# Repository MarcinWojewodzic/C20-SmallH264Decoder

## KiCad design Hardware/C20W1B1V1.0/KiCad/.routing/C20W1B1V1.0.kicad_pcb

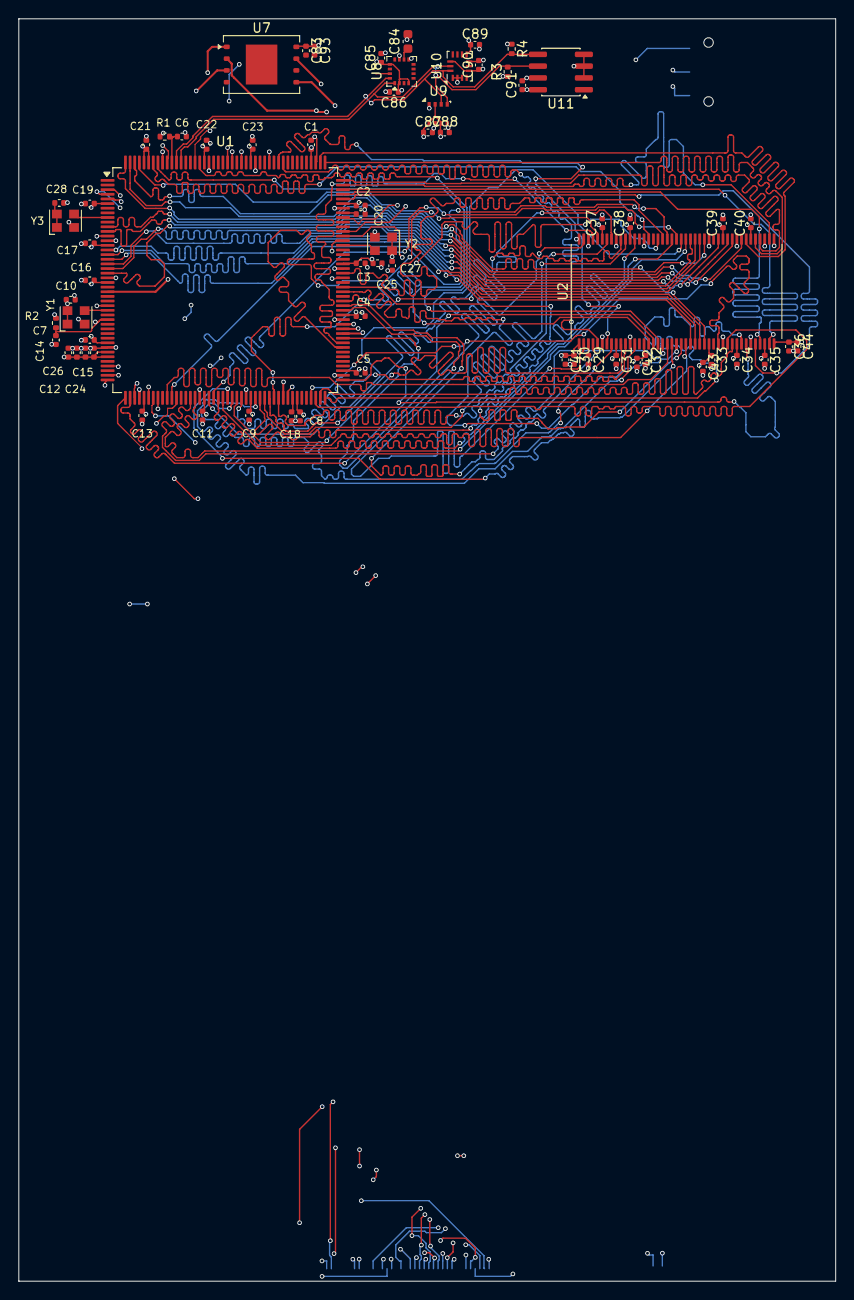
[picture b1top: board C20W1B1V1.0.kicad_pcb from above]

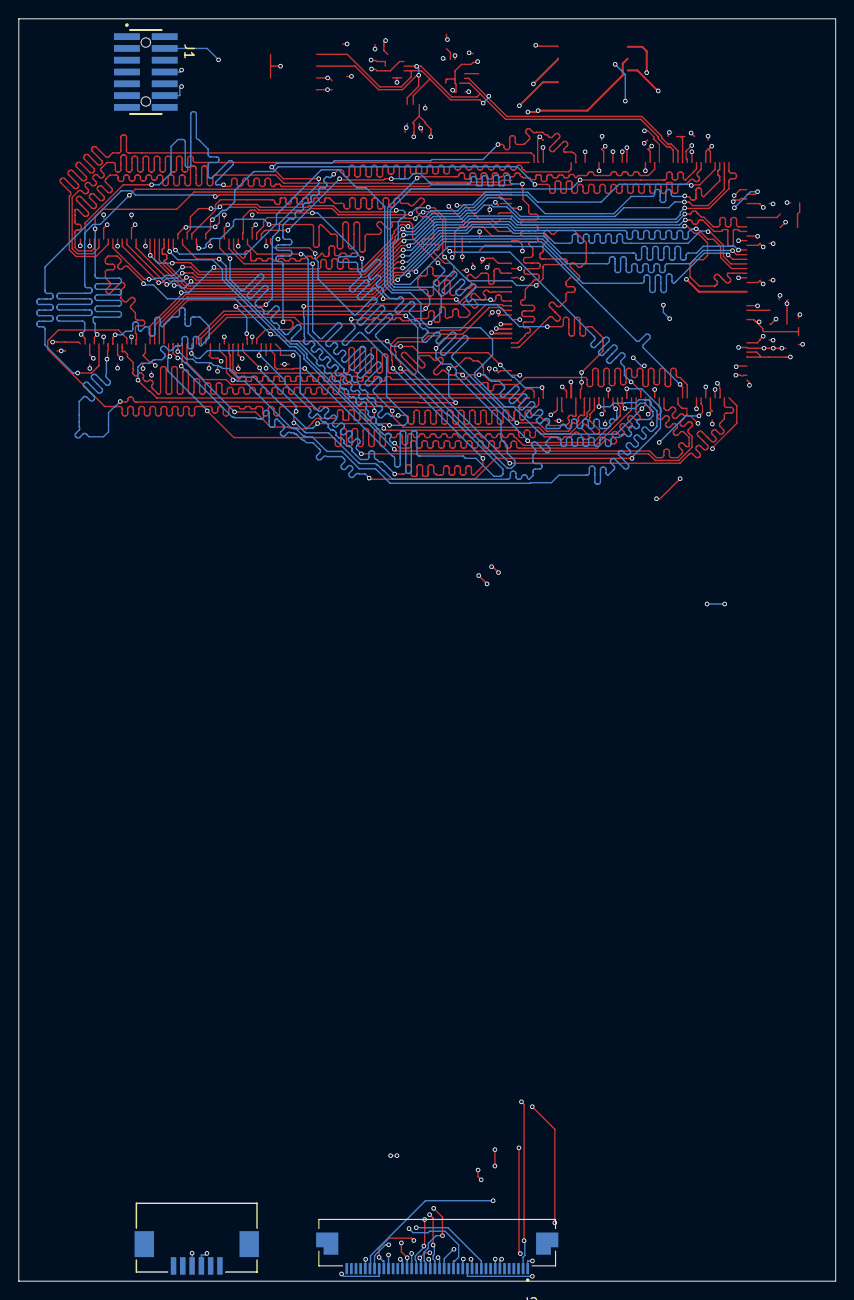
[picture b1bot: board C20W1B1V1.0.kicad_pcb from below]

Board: 6 copper layers, 88.0 x 136.0 mm, 71 parts (3 on the bottom side), 110 nets.

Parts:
C1, C2, C3, C4, C5, C6, C7, C8, C9, C10, C11, C13, C14, C15, C16, C17, C19, C21, C22, C23, C24, C27, C28, C29, C30, C31, C32, C33, C34, C35, C36, C37, C38, C39, C40, C83: 100n/50V/X5R; C_0402_1005Metric
C12, C18, C20, C25, C26, C41, C42, C43, C44, C93: 2u2/10V/X5R; C_0402_1005Metric
C84: 10u/10V/X5R; C_0603_1608Metric
C85, C86, C87, C88, C89, C90, C91: 4.7u/10V/X5R; C_0402_1005Metric
J1: FTSH-107-01-L-DV-K-A; SAMTEC_FTSH-107-01-L-DV-K-A
J2: 62684-402100ALF; AMPHENOL_62684-402100ALF
J3: 0522710679; CON_522710679_MOL
R1, R2: 10k/1%/0.063W; R_0402_1005Metric
R3, R4: 4k7/1%/0.063W; R_0402_1005Metric
U1: STM32H753IITx; LQFP-176_24x24mm_P0.5mm
U2: IS45S32400J-6TLA1-TR; TSOP-II-86_10.16x22.22mm_P0.5mm_ISSI
U7: W25R256JVEIQ; WSON-8-1EP_8x6mm_P1.27mm_EP3.4x4.3mm
U8: MMC5983MA; LGA-16_3x3mm_P0.5mm
U9: BME280; Bosch_LGA-8_2.5x2.5mm_P0.65mm_ClockwisePinNumbering
U10: LSM6DSV80XTR; Bosch_LGA-14_3x2.5mm_P0.5mm
U11: FM24CL04B-GTR; SOIC-8_3.9x4.9mm_P1.27mm
Y1: XO22C3EREHX25M000; Oscillator_SMD_Kyocera_KC2520Z-4Pin_2.5x2.0mm
Y2: KC2520Z12.2880C1KX00; Oscillator_SMD_Kyocera_KC2520Z-4Pin_2.5x2.0mm
Y3: ECS-327MVATX-2-CN-TR; Oscillator_SMD_Kyocera_KC2520Z-4Pin_2.5x2.0mm

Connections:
+3V3: C1.1, C2.1, C3.1, C4.1, C5.1, C8.1, C9.1, C10.1, C11.1, C12.1, C13.1, C14.1, C15.1, C16.1, C17.1, C19.1, C21.1, C22.1, C23.1, C24.1, C25.1, C26.1, C27.1, C28.1, C29.1, C30.1, C31.1, C32.1, C33.1, C34.1, C35.1, C36.1, C37.1, C38.1, C39.1, C40.1, C41.1, C42.1, C43.1, C44.1, C83.1, C85.1, C86.1, C87.1, C88.1, C89.1, C90.1, C91.1, C93.1, J1.3 (VCC), J2.4, J3.1, R2.1, R3.1, R4.1, U1.6 (VBAT), U1.15 (VDD), U1.23 (VDD), U1.36 (VDD), U1.38 (VREF+), U1.39 (VDDA), U1.49 (VDD), U1.62 (VDD), U1.72 (VDD), U1.82 (VDD), U1.91 (VDD), U1.103 (VDD), U1.114 (VDD33_USB), U1.127 (VDD), U1.136 (VDD), U1.149 (VDD), U1.159 (VDD), U1.171 (PDR_ON), U1.172 (VDD), U2.1 (VDD), U2.3 (VDDQ), U2.9 (VDDQ), U2.15 (VDD), U2.29 (VDD), U2.35 (VDDQ), U2.41 (VDDQ), U2.43 (VDD), U2.49 (VDDQ), U2.55 (VDDQ), U2.75 (VDDQ), U2.81 (VDDQ), U7.8 (VCC), U8.2 (VDD), U8.4 (SPI_CS), U8.13 (VDDIO), U9.2 (CSB), U9.6 (VDDIO), U9.8 (VDD), U10.5 (VDDIO), U10.8 (VDD), U10.12 (CS), U11.8 (VDD), Y1.1 (INH), Y1.4 (VCC), Y2.1 (INH), Y2.4 (VCC), Y3.1 (INH), Y3.4 (VCC)
/uC/RX: J1.14 (VCP_TX), U1.140 (PC11)
/uC/STM_NRST: C7.1, J1.12 (~RST), R2.2, U1.31 (NRST)
/uC/SWCLK: J1.6 (JCLK/SWCLK), U1.137 (PA14)
/uC/SWDIO: J1.4 (JTMS/SWDIO), U1.124 (PA13)
/uC/SWO: J1.8 (JTDO/SWO), U1.161 (PB3)
/uC/TX: J1.13 (VCP_RX), U1.139 (PC10)
FMC_A0: U1.16 (PF0), U2.25 (A0)
FMC_A1: U1.17 (PF1), U2.26 (A1)
FMC_A2: U1.18 (PF2), U2.27 (A2)
FMC_A3: U1.19 (PF3), U2.60 (A3)
FMC_A4: U1.20 (PF4), U2.61 (A4)
FMC_A5: U1.21 (PF5), U2.62 (A5)
FMC_A6: U1.60 (PF12), U2.63 (A6)
FMC_A7: U1.63 (PF13), U2.64 (A7)
FMC_A8: U1.64 (PF14), U2.65 (A8)
FMC_A9: U1.65 (PF15), U2.66 (A9)
FMC_A10: U1.66 (PG0), U2.24 (A10)
FMC_A11: U1.67 (PG1), U2.21 (A11)
FMC_A12: U1.106 (PG2), U2.69 (A12/NC)
FMC_BA0: U1.108 (PG4), U2.22 (BA0)
FMC_BA1: U1.109 (PG5), U2.23 (BA1)
FMC_CKE: U1.55 (PC5), U2.67 (CKE)
FMC_CLK: U1.112 (PG8), U2.68 (CLK)
FMC_DQ0: U1.104 (PD14), U2.2 (DQ0)
FMC_DQ1: U1.105 (PD15), U2.4 (DQ1)
FMC_DQ2: U1.142 (PD0), U2.5 (DQ2)
FMC_DQ3: U1.143 (PD1), U2.7 (DQ3)
FMC_DQ4: U1.68 (PE7), U2.8 (DQ4)
FMC_DQ5: U1.69 (PE8), U2.10 (DQ5)
FMC_DQ6: U1.70 (PE9), U2.11 (DQ6)
FMC_DQ7: U1.73 (PE10), U2.13 (DQ7)
FMC_DQ8: U1.74 (PE11), U2.74 (DQ8)
FMC_DQ9: U1.75 (PE12), U2.76 (DQ9)
FMC_DQ10: U1.76 (PE13), U2.77 (DQ10)
FMC_DQ11: U1.77 (PE14), U2.79 (DQ11)
FMC_DQ12: U1.78 (PE15), U2.80 (DQ12)
FMC_DQ13: U1.96 (PD8), U2.82 (DQ13)
FMC_DQ14: U1.97 (PD9), U2.83 (DQ14)
FMC_DQ15: U1.98 (PD10), U2.85 (DQ15)
FMC_DQ16: U1.85 (PH8), U2.31 (DQ16)
FMC_DQ17: U1.86 (PH9), U2.33 (DQ17)
FMC_DQ18: U1.87 (PH10), U2.34 (DQ18)
FMC_DQ19: U1.88 (PH11), U2.36 (DQ19)
FMC_DQ20: U1.89 (PH12), U2.37 (DQ20)
FMC_DQ21: U1.128 (PH13), U2.39 (DQ21)
FMC_DQ22: U1.129 (PH14), U2.40 (DQ22)
FMC_DQ23: U1.130 (PH15), U2.42 (DQ23)
FMC_DQ24: U1.131 (PI0), U2.45 (DQ24)
FMC_DQ25: U1.132 (PI1), U2.47 (DQ25)
FMC_DQ26: U1.133 (PI2), U2.48 (DQ26)
FMC_DQ27: U1.134 (PI3), U2.50 (DQ27)
FMC_DQ28: U1.175 (PI6), U2.51 (DQ28)
FMC_DQ29: U1.176 (PI7), U2.53 (DQ29)
FMC_DQ30: U1.11 (PI9), U2.54 (DQ30)
FMC_DQ31: U1.12 (PI10), U2.56 (DQ31)
FMC_DQM0: U1.169 (PE0), U2.16 (DQM0)
FMC_DQM1: U1.170 (PE1), U2.71 (DQM1)
FMC_DQM2: U1.173 (PI4), U2.28 (DQM2)
FMC_DQM3: U1.174 (PI5), U2.59 (DQM3)
FMC_~CAS: U1.160 (PG15), U2.18 (~CAS)
FMC_~CS: U1.54 (PC4), U2.20 (~CS)
FMC_~RAS: U1.59 (PF11), U2.19 (~RAS)
FMC_~WE: U1.46 (PH5), U2.17 (~WE)
GND: C1.2, C2.2, C3.2, C4.2, C5.2, C6.2, C7.2, C8.2, C9.2, C10.2, C11.2, C12.2, C13.2, C14.2, C15.2, C16.2, C17.2, C18.2, C19.2, C20.2, C21.2, C22.2, C23.2, C24.2, C25.2, C26.2, C27.2, C28.2, C29.2, C30.2, C31.2, C32.2, C33.2, C34.2, C35.2, C36.2, C37.2, C38.2, C39.2, C40.2, C41.2, C42.2, C43.2, C44.2, C83.2, C84.2, C85.2, C86.2, C87.2, C88.2, C89.2, C90.2, C91.2, C93.2, J1.5 (GND), J1.7 (GND), J1.11 (GNDDetect), J2.3, J2.29, J2.36, J2.41 (MH), J3.2, J3.7, R1.2, U1.14 (VSS), U1.22 (VSS), U1.37 (VSSA), U1.48 (VSS), U1.61 (VSS), U1.71 (VSS), U1.90 (VSS), U1.102 (VSS), U1.113 (VSS), U1.126 (VSS), U1.135 (VSS), U1.148 (VSS), U1.158 (VSS), U2.6 (VSSQ), U2.12 (VSSQ), U2.32 (VSSQ), U2.38 (VSSQ), U2.44 (VSS), U2.46 (VSSQ), U2.52 (VSSQ), U2.58 (VSS), U2.72 (VSS), U2.78 (VSSQ), U2.84 (VSSQ), U2.86 (VSS), U7.4 (GND), U7.9 (EP), U8.9 (GND), U8.11 (GND), U9.1 (GND), U9.5 (SDO), U9.7 (GND), U10.1 (SDO/SA0), U10.2 (SDX), U10.3 (SCX), U10.6 (GND), U10.7 (GND), U11.2 (A1), U11.3 (A2), U11.4 (GND), U11.7 (WP), Y1.2 (GND), Y2.2 (GND), Y3.2 (GND)
LTDC_B0: J2.21, U1.3 (PE4)
LTDC_B1: J2.22, U1.121 (PA10)
LTDC_B2: J2.23, U1.150 (PD6)
LTDC_B3: J2.24, U1.119 (PA8)
LTDC_B4: J2.25, U1.155 (PG12)
LTDC_B5: J2.26, U1.47 (PA3)
LTDC_B6: J2.27, U1.167 (PB8)
LTDC_B7: J2.28, U1.168 (PB9)
LTDC_CLK: J2.30, U1.111 (PG7)
LTDC_DE: J2.34, U1.28 (PF10)
LTDC_G0: J2.13, U1.4 (PE5)
LTDC_G1: J2.14, U1.5 (PE6)
LTDC_G2: J2.15, U1.52 (PA6)
LTDC_G3: J2.16, U1.153 (PG10)
LTDC_G4: J2.17, U1.45 (PH4)
LTDC_G5: J2.18, U1.80 (PB11)
LTDC_G6: J2.19, U1.13 (PI11)
LTDC_G7: J2.20, U1.145 (PD3)
LTDC_HS: J2.32, U1.115 (PC6)
LTDC_R0: J2.5, U1.43 (PH2)
LTDC_R1: J2.6, U1.44 (PH3)
LTDC_R2: J2.7, U1.41 (PA1)
LTDC_R3: J2.8, U1.56 (PB0)
LTDC_R4: J2.9, U1.51 (PA5)
LTDC_R5: J2.10, U1.120 (PA9)
LTDC_R6: J2.11, U1.57 (PB1)
LTDC_R7: J2.12, U1.110 (PG6)
LTDC_VS: J2.33, U1.50 (PA4)
unnamed: C18.1, U1.81 (VCAP)
unnamed: C20.1, U1.125 (VCAP)
unnamed: C6.1, R1.1, U1.166 (BOOT0)
unnamed: U1.118 (PC9), Y2.3 (CLK)
unnamed: U1.9 (PC14), Y3.3 (CLK)
unnamed: U1.29 (PH0), Y1.3 (CLK)
unnamed: C84.1, U8.10 (CAP)
QSPI_CLK: U1.58 (PB2), U7.6 (CLK)
QSPI_CS: U1.79 (PB10), U7.1 (~CS)
QSPI_IO0: U1.99 (PD11), U7.5 (DI/IO_{0})
QSPI_IO1: U1.100 (PD12), U7.2 (DO/IO_{1})
QSPI_IO2: U1.25 (PF7), U7.3 (~WP/IO_{2})
QSPI_IO3: U1.101 (PD13), U7.7 (~HOLD/~RESET/IO_{3})
SCL: J3.3, R3.2, U1.164 (PB6), U8.1 (SCL/SPI_SCK), U9.4 (SCK), U10.13 (SCL), U11.6 (SCL)
SDA: J3.4, R4.2, U1.165 (PB7), U8.16 (SDA/SPI_SDI), U9.3 (SDI), U10.14 (SDA), U11.5 (SDA)
TFT_CLK_SPI: J2.39, U1.154 (PG11)
TFT_DATA_SPI: J2.40, U1.151 (PD7)
